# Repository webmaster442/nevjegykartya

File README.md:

# Ruzsinszki Gábor névjegykártya

2019-es Névjegykártya terv. A névjegykártyán a kapcsolás egy USBTinyISP SMD klón, így az eredeti driver és firmware segítségével működtethető. A terv elkészítéséhez Eagle PCB szoftvert használtam.

## Linkek: 

* USBTinyISP: https://learn.adafruit.com/usbtinyisp
* Eagle: https://www.autodesk.com/products/eagle/overview
* JLCPCB: https://jlcpcb.com/ 

## Licenc

**Nyomtatott áramkör és kapcsolási rajz**: Creative Commons Nevezd meg! - Így add tovább! 4.0
https://creativecommons.org/licenses/by-sa/4.0/deed.hu

**Firmware:** GPL http://gnu.hu/gpl.html

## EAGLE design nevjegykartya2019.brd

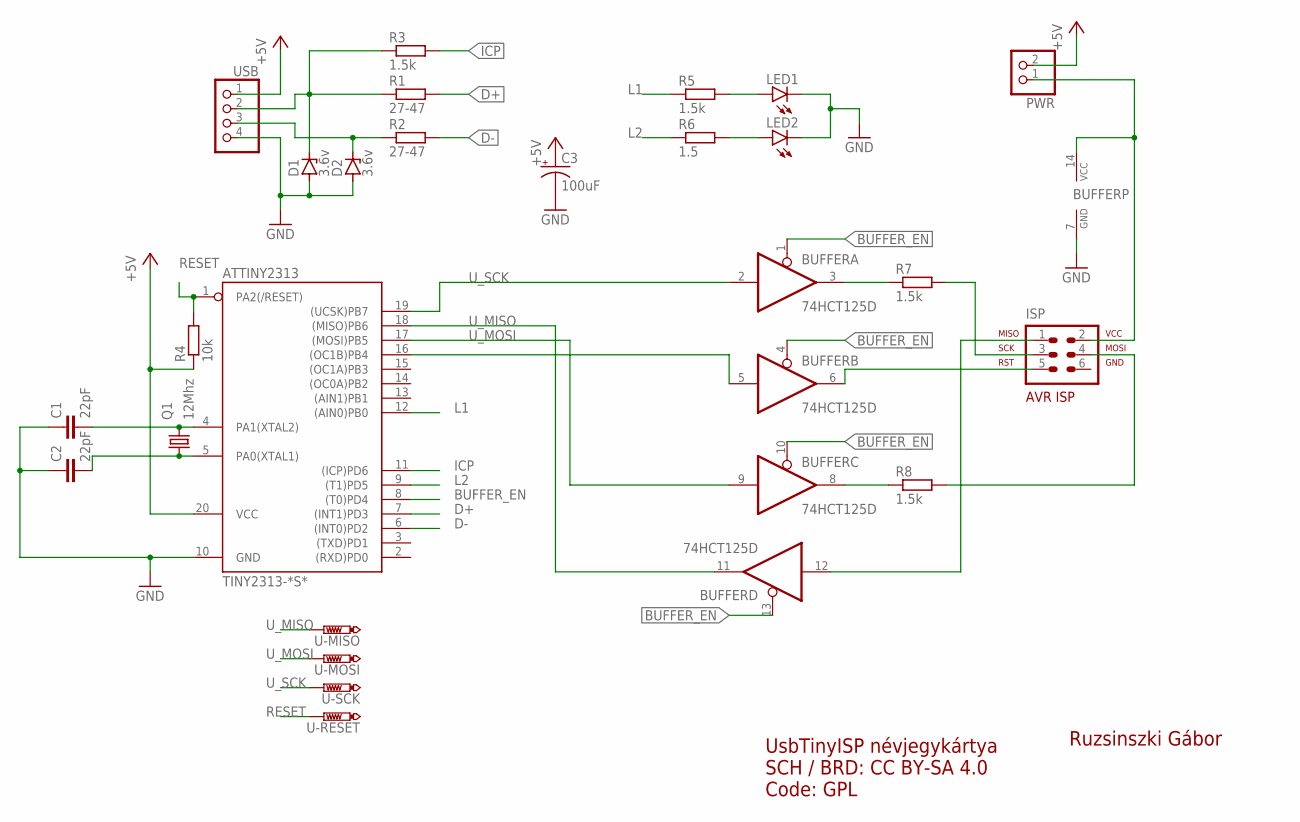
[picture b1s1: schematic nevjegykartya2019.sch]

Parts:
ATTINY2313: TINY2313-*S*; SO20L$
BUFFER: 74HCT125D; SO14
C1, C2: 22pF; C1206
C3: 100uF; E2,5-5
D1, D2: 3.6v; SOT223
ISP: AVR-ISP-6VERT; AVR-ISP-6
LED1, LED2: LEDCHIPLED_1206; CHIPLED_1206
PWR: PINHD-1X2/90; 1X02/90
Q1: 12Mhz; 6.0X3.5_2
R1, R2: 27-47; M1206
R3, R5, R7, R8: 1.5k; M1206
R4: 10k; M1206
R6: 1.5; M1206
U-MISO: PTR1TP20SQ; TP20SQ
U-MOSI: PTR1TP20SQ; TP20SQ
U-RESET: PTR1TP20SQ; TP20SQ
U-SCK: PTR1TP20SQ; TP20SQ
USB: PINHD-1X4/90; 1X04/90

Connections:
+5V: ATTINY2313.20 (VCC), C3.+, PWR.2, R4.1, USB.1
BUFFER_EN: ATTINY2313.8 ((T0)PD4), BUFFER.1 (OE), BUFFER.4 (OE), BUFFER.10 (OE), BUFFER.13 (OE)
D+: ATTINY2313.7 ((INT1)PD3), R1.2
D-: ATTINY2313.6 ((INT0)PD2), R2.2
GND: ATTINY2313.10 (GND), BUFFER.7 (GND), C1.1, C2.1, C3.-, D1.1 (A), D2.1 (A), LED1.C, LED2.C, USB.4
ICP: ATTINY2313.11 ((ICP)PD6), R3.2
L1: ATTINY2313.12 ((AIN0)PB0), R5.1
L2: ATTINY2313.9 ((T1)PD5), R6.1
MISO: BUFFER.12 (I), ISP.1
MOSI: ISP.4, R8.2
unnamed: LED2.A, R6.2
unnamed: D1.4 (C), R1.1, R3.1, USB.2
unnamed: D2.4 (C), R2.1, USB.3
unnamed: LED1.A, R5.2
unnamed: BUFFER.8 (O), R8.1
unnamed: BUFFER.3 (O), R7.1
unnamed: ATTINY2313.16 ((OC1B)PB4), BUFFER.5 (I)
unnamed: ATTINY2313.4 (PA1(XTAL2)), C1.2, Q1.2
unnamed: BUFFER.14 (VCC), ISP.2, PWR.1
unnamed: ATTINY2313.5 (PA0(XTAL1)), C2.2, Q1.1
RESET: ATTINY2313.1 (PA2(/RESET)), R4.2, U-RESET.TP
RST: BUFFER.6 (O), ISP.5
SCK: ISP.3, R7.2
U_MISO: ATTINY2313.18 ((MISO)PB6), BUFFER.11 (O), U-MISO.TP
U_MOSI: ATTINY2313.17 ((MOSI)PB5), BUFFER.9 (I), U-MOSI.TP
U_SCK: ATTINY2313.19 ((UCSK)PB7), BUFFER.2 (I), U-SCK.TP

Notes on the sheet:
Ruzsinszki Gábor
UsbTinyISP névjegykártya SCH / BRD: CC BY-SA 4.0 Code: GPL

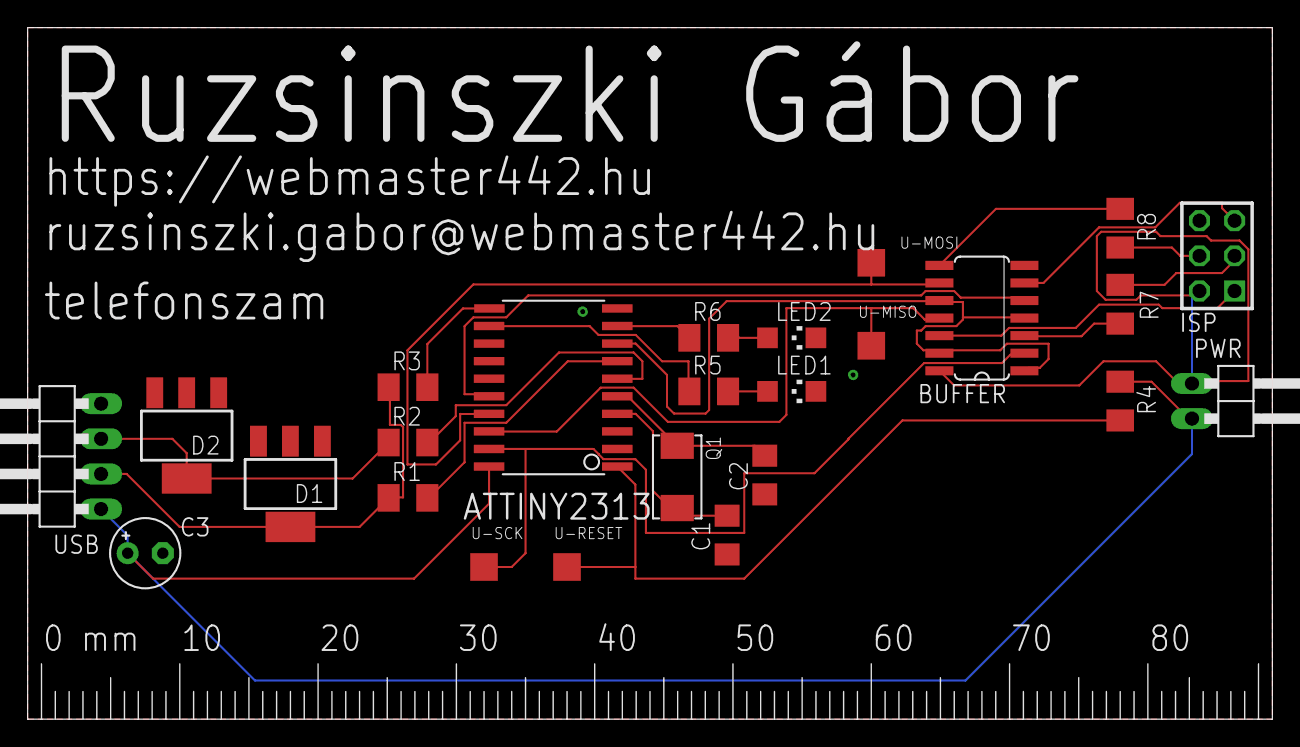
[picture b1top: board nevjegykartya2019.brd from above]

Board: 2 copper layers, 90.0 x 50.0 mm, 25 parts (0 on the bottom side), 26 nets.

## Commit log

2019-09-10 Névjegykártya 2019
2019-09-16 Readme frissítés
2019-09-16 Kapcsolási rajz pdf formátum

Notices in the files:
parts and their libraries:
crystal-geyer_V1_0: Copyright: Geyer-Electronic
